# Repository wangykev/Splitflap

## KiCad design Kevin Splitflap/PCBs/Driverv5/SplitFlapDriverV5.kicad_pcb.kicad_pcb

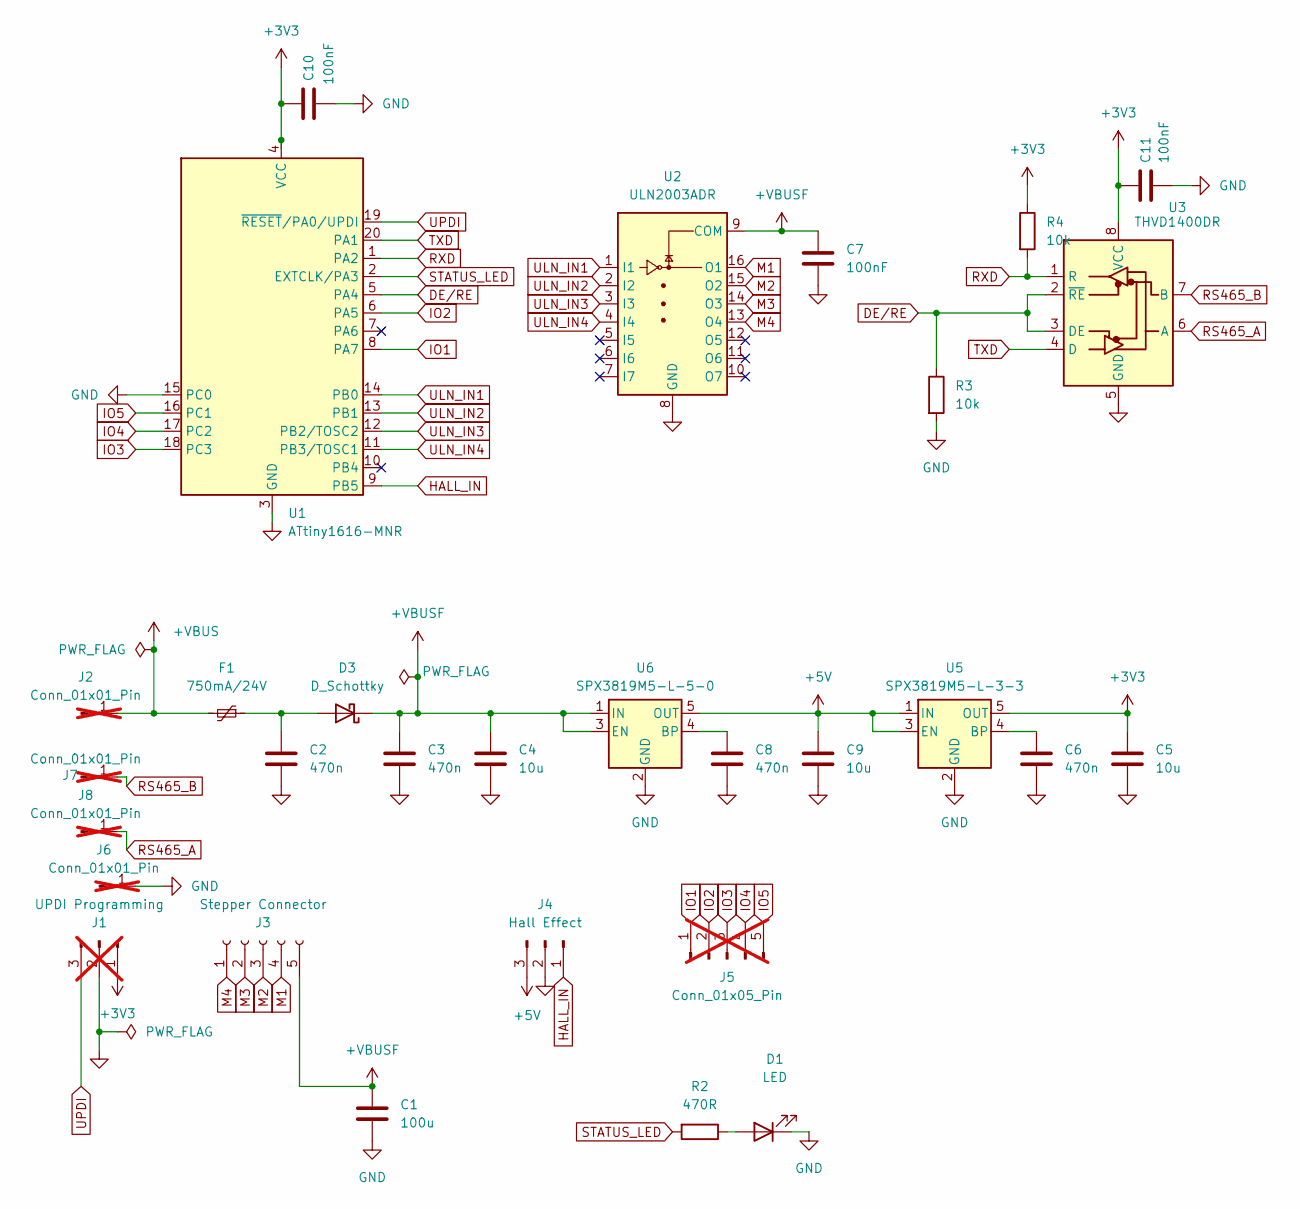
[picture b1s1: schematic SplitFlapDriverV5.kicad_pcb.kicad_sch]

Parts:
C1: 100u; CP_Elec_6.3x5.4; JLCPCB Part Number C4747964
C2, C3, C6, C8: 470n; C_0603_1608Metric; JLCPCB Part Number C1623
C4: 10u; C_0805_2012Metric; JLCPCB Part Number C15850
C5, C9: 10u; C_0603_1608Metric; JLCPCB Part Number C19702
C7, C10, C11: 100nF; C_0603_1608Metric; JLCPCB Part Number C14663
D1: LED; LED_0603_1608Metric; JLCPCB Part Number C2286
D3: D_Schottky; D_SMA; JLCPCB Part Number C8678
F1: 750mA/24V; Fuse_1812_4532Metric; JLCPCB Part Number C12557
J1: UPDI Programming; PinHeader_1x03_P2.54mm_Vertical; not fitted
J2, J6, J7, J8: Conn_01x01_Pin; PinHeader_1x01_P2.54mm_Vertical; not fitted
J3: Stepper Connector; JST_XH_B5B-XH-A_1x05_P2.50mm_Vertical; JLCPCB Part Number C157991
J4: Hall Effect; JST_PH_B3B-PH-K_1x03_P2.00mm_Vertical; JLCPCB Part Number C131339
J5: Conn_01x05_Pin; PinHeader_1x05_P2.54mm_Vertical; not fitted
R2: 470R; R_0603_1608Metric; JLCPCB Part Number C23179
R3, R4: 10k; R_0603_1608Metric; JLCPCB Part Number C25804
U1: ATtiny1616-MNR; VQFN-20-1EP_3x3mm_P0.4mm_EP1.7x1.7mm; Manufacturer Part Number ATTINY1616-MNR; JLCPCB Part Number C507118
U2: ULN2003ADR; SOIC-16_3.9x9.9mm_P1.27mm; Manufacturer Part Number ULN2003ADR; JLCPCB Part Number C7512
U3: THVD1400DR; SOIC-8_3.9x4.9mm_P1.27mm; Manufacturer Part Number THVD1400DR; JLCPCB Part Number C3235232
U5: SPX3819M5-L-3-3; SOT-23-5; JLCPCB Part Number C9055
U6: SPX3819M5-L-5-0; SOT-23-5; JLCPCB Part Number C13417

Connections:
+3V3: C5.1, C10.1, C11.1, J1.1, R4.1, U1.4 (VCC), U3.8 (VCC), U5.5 (OUT)
+5V: C9.1, J4.3, U5.1 (IN), U5.3 (EN), U6.5 (OUT)
+VBUS: F1.2, J2.1 (Pin_1_1)
+VBUSF: C1.1, C3.1, C4.1, C7.1, D3.1 (K), J3.5, U2.9 (COM), U6.1 (IN), U6.3 (EN)
DE/RE: R3.1, U1.5 (PA4), U3.2 (~RE), U3.3 (DE)
GND: C1.2, C2.2, C3.2, C4.2, C5.2, C6.2, C7.2, C8.2, C9.2, C10.2, C11.2, D1.1 (K), J1.2, J4.2, J6.1 (Pin_1_1), R3.2, U1.3 (GND), U1.15 (PC0), U2.8 (GND), U3.5 (GND), U5.2 (GND), U6.2 (GND)
HALL_IN: J4.1, U1.9 (PB5)
IO1: J5.1, U1.8 (PA7)
IO2: J5.2, U1.6 (PA5)
IO3: J5.3, U1.18 (PC3)
IO4: J5.4, U1.17 (PC2)
IO5: J5.5, U1.16 (PC1)
M1: J3.4, U2.16 (O1)
M2: J3.3, U2.15 (O2)
M3: J3.2, U2.14 (O3)
M4: J3.1, U2.13 (O4)
unnamed: D1.2 (A), R2.1
unnamed: C2.1, D3.2 (A), F1.1
unnamed: C6.1, U5.4 (BP)
unnamed: C8.1, U6.4 (BP)
RS465_A: J8.1 (Pin_1_1), U3.6 (A)
RS465_B: J7.1 (Pin_1_1), U3.7 (B)
RXD: R4.2, U1.1 (PA2), U3.1 (R)
STATUS_LED: R2.2, U1.2 (EXTCLK/PA3)
TXD: U1.20 (PA1), U3.4 (D)
ULN_IN1: U1.14 (PB0), U2.1 (I1)
ULN_IN2: U1.13 (PB1), U2.2 (I2)
ULN_IN3: U1.12 (PB2/TOSC2), U2.3 (I3)
ULN_IN4: U1.11 (PB3/TOSC1), U2.4 (I4)
UPDI: J1.3, U1.19 (~RESET/PA0/UPDI)

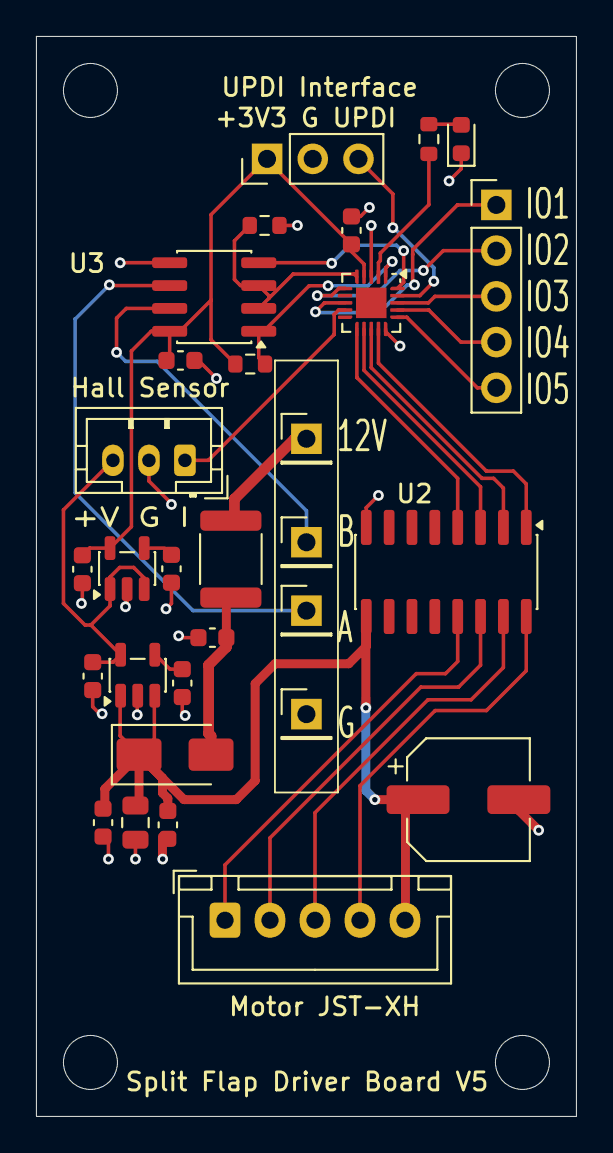
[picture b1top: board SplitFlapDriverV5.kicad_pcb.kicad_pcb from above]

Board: 2 copper layers, 30.0 x 60.0 mm, 30 parts (0 on the bottom side), 30 nets.

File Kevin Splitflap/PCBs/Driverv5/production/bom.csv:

Designator,Footprint,Quantity,Value,LCSC Part #
C1,CP_Elec_6.3x5.4,1,100u,C4747964
"C10, C11, C7",0603,3,100nF,C14663
"C2, C3, C6, C8",0603,4,470n,C1623
C4,0805,1,10u,C15850
"C5, C9",0603,2,10u,C19702
D1,0603,1,LED,C2286
D3,D_SMA,1,D_Schottky,C8678
F1,1812,1,750mA/24V,C12557
J3,JST_XH_B5B-XH-A_1x05_P2.50mm_Vertical,1,Stepper Connector,C157991
J4,JST_PH_B3B-PH-K_1x03_P2.00mm_Vertical,1,Hall Effect,C131339
R2,0603,1,470R,C23179
"R3, R4",0603,2,10k,C25804
U1,VQFN-20-1EP_3x3mm_P0.4mm_EP1.7x1.7mm,1,ATtiny1616-MNR,C507118
U2,SOIC-16_3.9x9.9mm_P1.27mm,1,ULN2003ADR,C7512
U3,SOIC-8_3.9x4.9mm_P1.27mm,1,THVD1400DR,C3235232
U5,SOT-23-5,1,SPX3819M5-L-3-3,C9055
U6,SOT-23-5,1,SPX3819M5-L-5-0,C13417

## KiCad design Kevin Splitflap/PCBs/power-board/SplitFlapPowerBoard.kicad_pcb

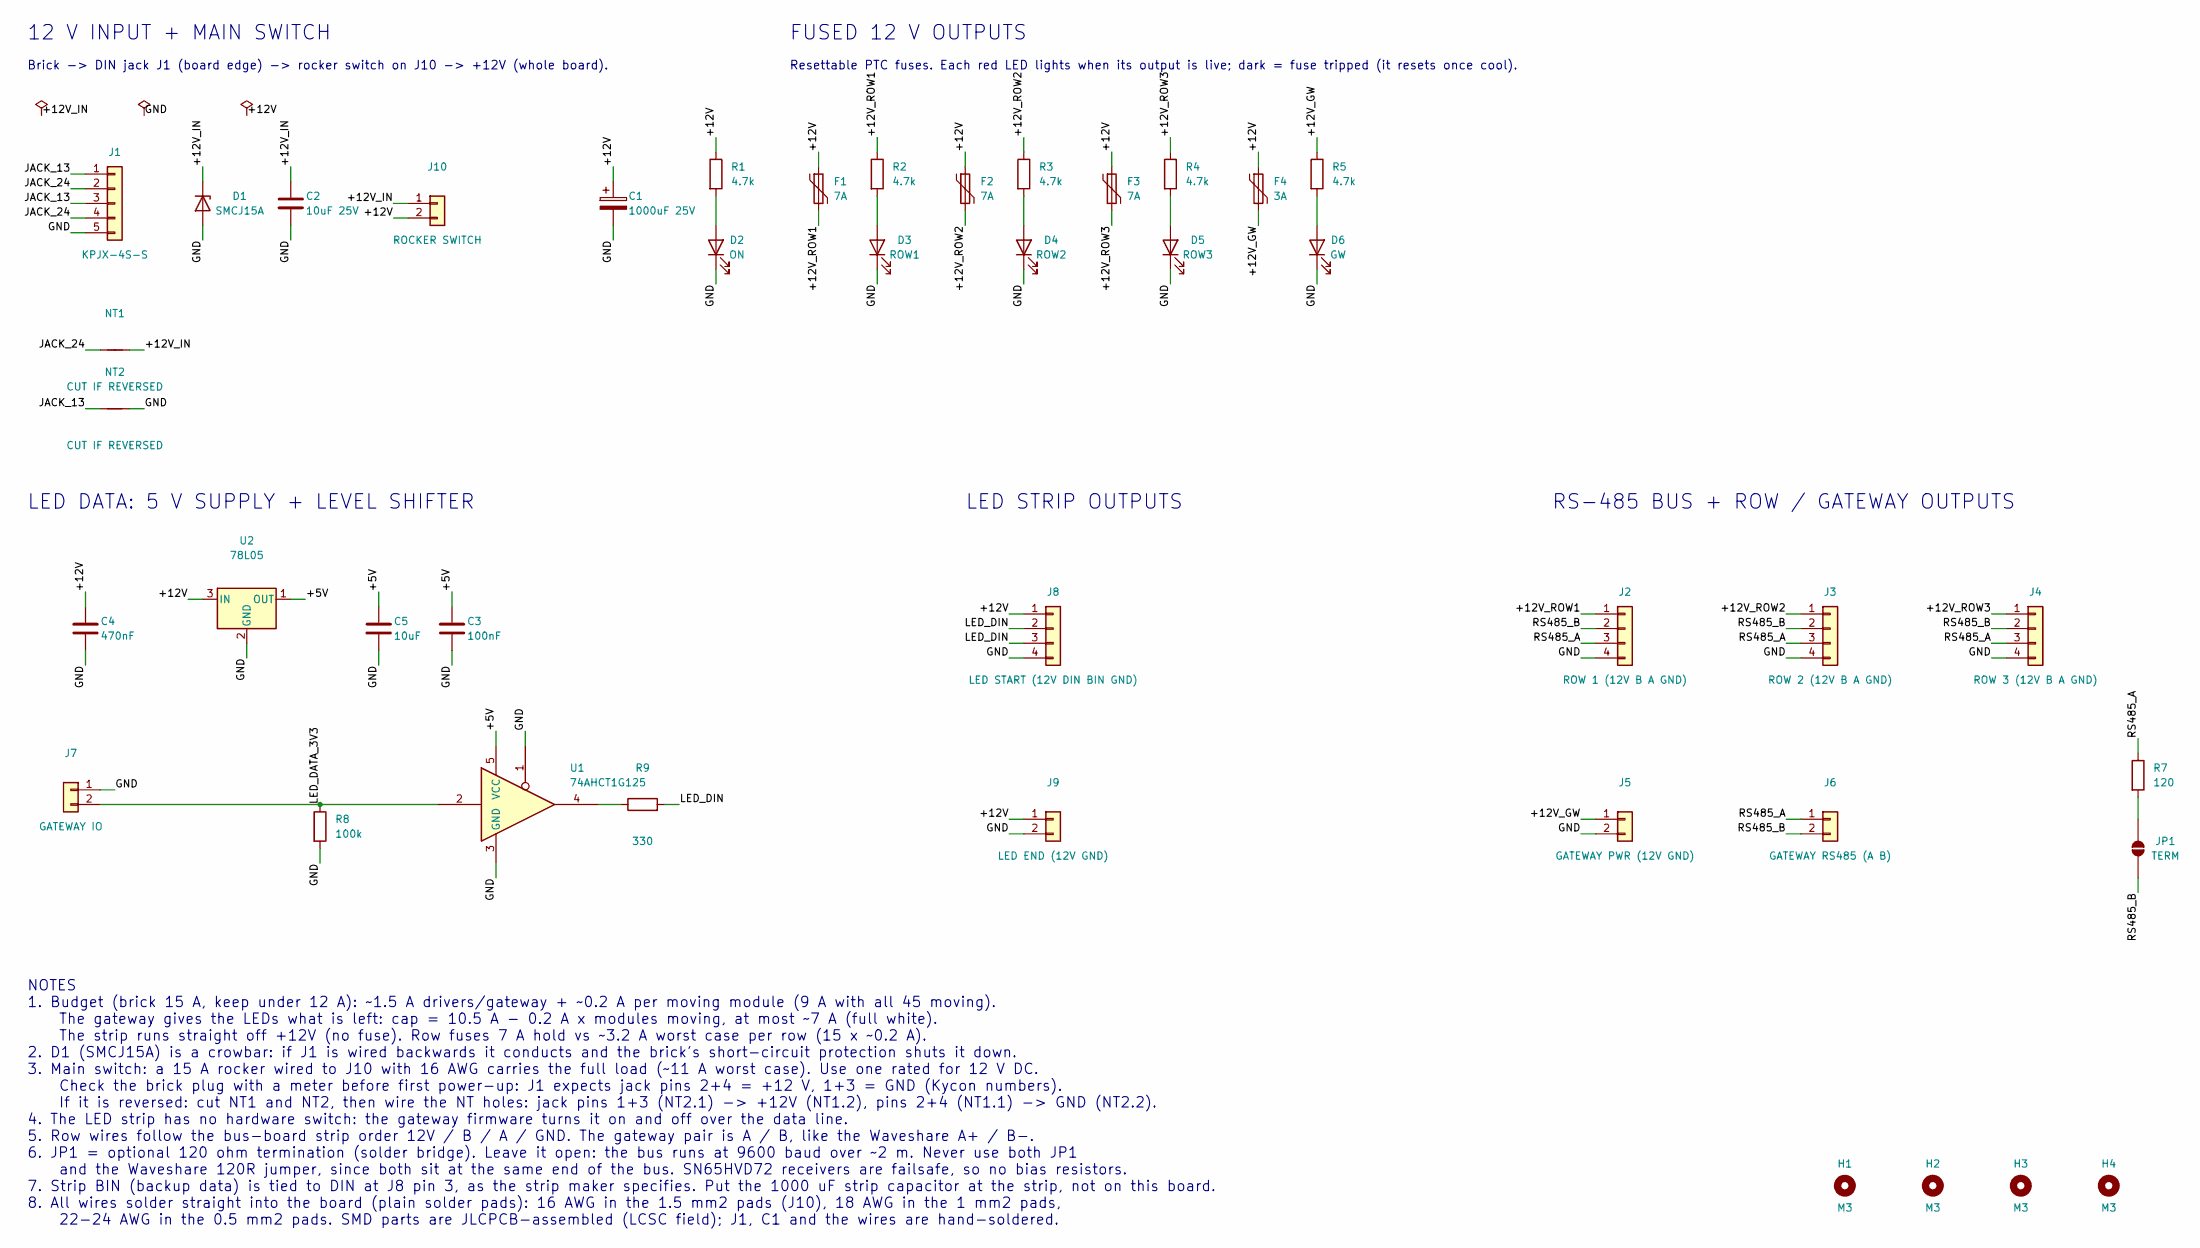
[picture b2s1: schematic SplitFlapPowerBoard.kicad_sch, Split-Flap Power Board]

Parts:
C1: 1000uF 25V; CP_Radial_D10.0mm_P5.00mm
C2: 10uF 25V; C_0805_2012Metric; LCSC C15850
C3: 100nF; C_0603_1608Metric; LCSC C14663
C4: 470nF; C_0603_1608Metric; LCSC C1623
C5: 10uF; C_0805_2012Metric; LCSC C15850
D1: SMCJ15A; D_SMC; LCSC C310016
D2: ON; LED_0603_1608Metric; LCSC C2286
D3: ROW1; LED_0603_1608Metric; LCSC C2286
D4: ROW2; LED_0603_1608Metric; LCSC C2286
D5: ROW3; LED_0603_1608Metric; LCSC C2286
D6: GW; LED_0603_1608Metric; LCSC C2286
F1, F2, F3: 7A; Fuse_2920_7451Metric; LCSC C22363536
F4: 3A; Fuse_2920_7451Metric; LCSC C39831901
H1, H2, H3, H4: M3; MountingHole_3.2mm_M3
J1: KPJX-4S-S; Kycon_KPJX-4S-S
J2: ROW 1 (12V B A GND); SolderWire-1sqmm_1x04_P5.4mm_D1.4mm_OD2.7mm
J3: ROW 2 (12V B A GND); SolderWire-1sqmm_1x04_P5.4mm_D1.4mm_OD2.7mm
J4: ROW 3 (12V B A GND); SolderWire-1sqmm_1x04_P5.4mm_D1.4mm_OD2.7mm
J5: GATEWAY PWR (12V GND); SolderWire-1sqmm_1x02_P5.4mm_D1.4mm_OD2.7mm
J6: GATEWAY RS485 (A B); SolderWire-0.5sqmm_1x02_P4.6mm_D0.9mm_OD2.1mm
J7: GATEWAY IO; SolderWire-0.5sqmm_1x02_P4.6mm_D0.9mm_OD2.1mm
J8: LED START (12V DIN BIN GND); SolderWire-1sqmm_1x04_P5.4mm_D1.4mm_OD2.7mm
J9: LED END (12V GND); SolderWire-1sqmm_1x02_P5.4mm_D1.4mm_OD2.7mm
J10: ROCKER SWITCH; SolderWire-1.5sqmm_1x02_P7.8mm_D1.7mm_OD3.9mm
JP1: TERM; SolderJumper-2_P1.3mm_Open_RoundedPad1.0x1.5mm
NT1, NT2: CUT IF REVERSED; CutLink_Holes_P6mm
R1, R2, R3, R4, R5: 4.7k; R_0603_1608Metric; LCSC C23162
R7: 120; R_0603_1608Metric; LCSC C22787
R8: 100k; R_0603_1608Metric; LCSC C25803
R9: 330; R_0603_1608Metric; LCSC C23138
U1: 74AHCT1G125; SOT-23-5; LCSC C7484
U2: 78L05; SOT-89-3; LCSC C71136

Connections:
/+5V: C3.1, C5.1, U1.5 (VCC), U2.1 (OUT)
/+12V: C1.1, C4.1, F1.1, F2.1, F3.1, F4.1, J8.1, J9.1, J10.2, R1.1, U2.3 (IN)
/+12V_GW: F4.2, J5.1, R5.1
/+12V_IN: C2.1, D1.1 (K), J10.1, NT1.2
/+12V_ROW1: F1.2, J2.1, R2.1
/+12V_ROW2: F2.2, J3.1, R3.1
/+12V_ROW3: F3.2, J4.1, R4.1
/GND: C1.2, C2.2, C3.2, C4.2, C5.2, D1.2 (A), D2.1 (K), D3.1 (K), D4.1 (K), D5.1 (K), D6.1 (K), J1.5, J2.4, J3.4, J4.4, J5.2, J7.1, J8.4, J9.2, NT2.2, R8.2, U1.1, U1.3 (GND), U2.2 (GND)
/JACK_13: J1.1, J1.3, NT2.1
/JACK_24: J1.2, J1.4, NT1.1
/LED_DATA_3V3: J7.2, R8.1, U1.2
/LED_DIN: J8.2, J8.3, R9.2
/RS485_A: J2.3, J3.3, J4.3, J6.1, R7.1
/RS485_B: J2.2, J3.2, J4.2, J6.2, JP1.1 (A)
unnamed: D2.2 (A), R1.2
unnamed: D3.2 (A), R2.2
unnamed: D4.2 (A), R3.2
unnamed: D5.2 (A), R4.2
unnamed: D6.2 (A), R5.2
unnamed: JP1.2 (B), R7.2
unnamed: R9.1, U1.4

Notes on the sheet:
12 V INPUT + MAIN SWITCH
Brick -> DIN jack J1 (board edge) -> rocker switch on J10 -> +12V (whole board).
FUSED 12 V OUTPUTS
Resettable PTC fuses. Each red LED lights when its output is live; dark = fuse tripped (it resets once cool).
LED DATA: 5 V SUPPLY + LEVEL SHIFTER
LED STRIP OUTPUTS
RS-485 BUS + ROW / GATEWAY OUTPUTS
NOTES 1. Budget (brick 15 A, keep under 12 A): ~1.5 A drivers/gateway + ~0.2 A per moving module (9 A with all 45 moving). The gateway gives the LEDs what is left: cap = 10.5 A - 0.2 A x modules moving, at most ~7 A (full white). The strip runs straight off +12V (no fuse). Row fuses 7 A hold vs ~3.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

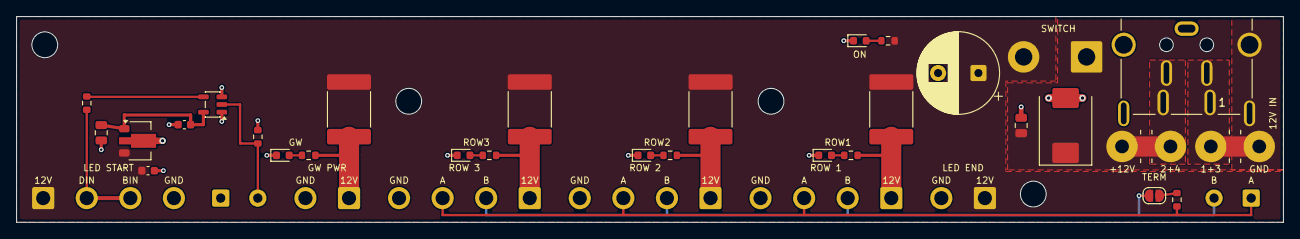
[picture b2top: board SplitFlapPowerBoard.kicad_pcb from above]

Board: 2 copper layers, 157.0 x 25.5 mm, 42 parts (0 on the bottom side), 21 nets.

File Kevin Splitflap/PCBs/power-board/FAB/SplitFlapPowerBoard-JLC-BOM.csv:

Comment,Designator,Footprint,LCSC Part #
"10uF 25V","C2,C5","C_0805_2012Metric","C15850"
"100nF","C3","C_0603_1608Metric","C14663"
"470nF","C4","C_0603_1608Metric","C1623"
"SMCJ15A","D1","D_SMC","C310016"
"ON","D2,D3,D4,D5,D6","LED_0603_1608Metric","C2286"
"7A","F1,F2,F3","Fuse_2920_7451Metric","C22363536"
"3A","F4","Fuse_2920_7451Metric","C39831901"
"4.7k","R1,R2,R3,R4,R5","R_0603_1608Metric","C23162"
"120","R7","R_0603_1608Metric","C22787"
"100k","R8","R_0603_1608Metric","C25803"
"330","R9","R_0603_1608Metric","C23138"
"74AHCT1G125","U1","SOT-23-5","C7484"
"78L05","U2","SOT-89-3","C71136"
